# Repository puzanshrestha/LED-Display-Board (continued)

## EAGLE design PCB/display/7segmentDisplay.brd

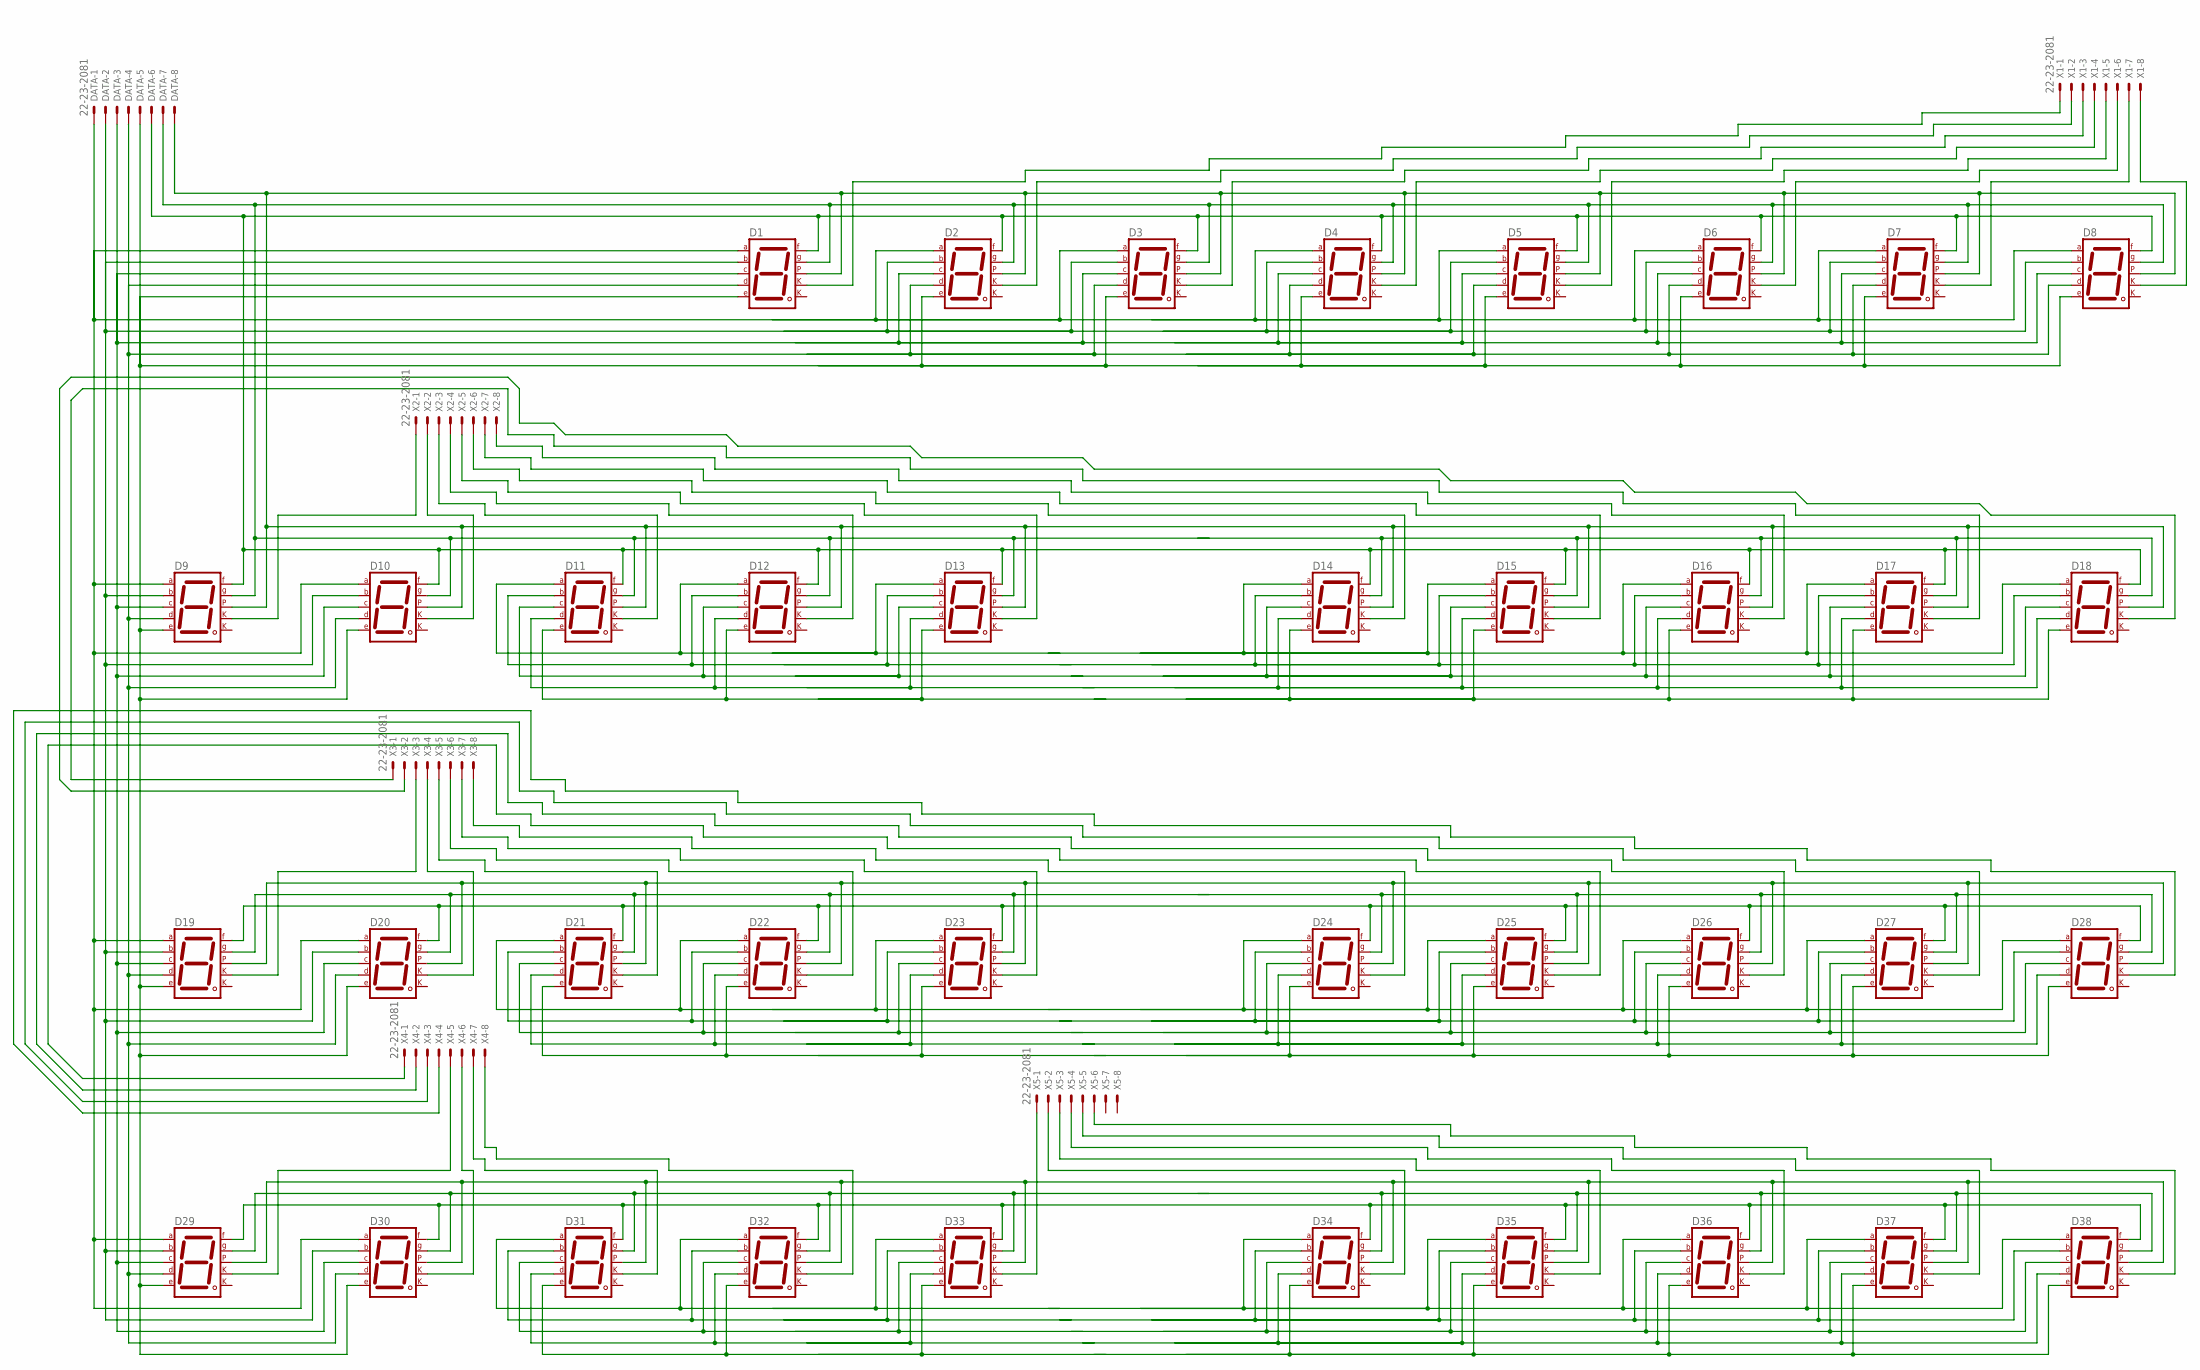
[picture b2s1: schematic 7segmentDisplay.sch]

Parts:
D1, D2, D3, D4, D5, D6, D7, D8, D9, D10, D11, D12, D13, D14, D15, D16, D17, D18, D19, D20, D21, D22, D23, D24, D25, D26, D27, D28, D29, D30, D31, D32, D33, D34, D35, D36, D37, D38: 7SEG-CK; 7SEG-13
DATA: 22-23-2081
X1, X2, X3, X4, X5: 22-23-2081

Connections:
unnamed: D1.7 (A), D2.7 (A), D3.7 (A), D4.7 (A), D5.7 (A), D6.7 (A), D7.7 (A), D8.7 (A), D9.7 (A), D10.7 (A), D19.7 (A), D20.7 (A), D29.7 (A), D30.7 (A), DATA.1
unnamed: D1.6 (B), D2.6 (B), D3.6 (B), D4.6 (B), D5.6 (B), D6.6 (B), D7.6 (B), D8.6 (B), D9.6 (B), D10.6 (B), D19.6 (B), D20.6 (B), D29.6 (B), D30.6 (B), DATA.2
unnamed: D1.4 (C), D2.4 (C), D3.4 (C), D4.4 (C), D5.4 (C), D6.4 (C), D7.4 (C), D8.4 (C), D9.4 (C), D10.4 (C), D19.4 (C), D20.4 (C), D29.4 (C), D30.4 (C), DATA.3
unnamed: D1.2 (D), D2.2 (D), D3.2 (D), D4.2 (D), D5.2 (D), D6.2 (D), D7.2 (D), D8.2 (D), D9.2 (D), D10.2 (D), D19.2 (D), D20.2 (D), D29.2 (D), D30.2 (D), DATA.4
unnamed: D1.1 (E), D2.1 (E), D3.1 (E), D4.1 (E), D5.1 (E), D6.1 (E), D7.1 (E), D8.1 (E), D9.1 (E), D10.1 (E), D19.1 (E), D20.1 (E), D29.1 (E), D30.1 (E), DATA.5
unnamed: D14.10 (G), D15.10 (G), D16.10 (G), D17.10 (G), D18.10 (G)
unnamed: D5.3 (CK1), X1.5
unnamed: D2.3 (CK1), X1.2
unnamed: D3.3 (CK1), X1.3
unnamed: D4.3 (CK1), X1.4
unnamed: D9.3 (CK1), X2.1
unnamed: D6.3 (CK1), X1.6
unnamed: D7.3 (CK1), X1.7
unnamed: D21.7 (A), D22.7 (A), D23.7 (A)
unnamed: D21.6 (B), D22.6 (B), D23.6 (B)
unnamed: D11.7 (A), D12.7 (A), D13.7 (A)
unnamed: D11.6 (B), D12.6 (B), D13.6 (B)
unnamed: D11.4 (C), D12.4 (C), D13.4 (C)
unnamed: D11.2 (D), D12.2 (D), D13.2 (D)
unnamed: D11.1 (E), D12.1 (E), D13.1 (E)
unnamed: D1.9 (F), D2.9 (F), D3.9 (F), D4.9 (F), D5.9 (F), D6.9 (F), D7.9 (F), D8.9 (F), D9.9 (F), D10.9 (F), D11.9 (F), D12.9 (F), D13.9 (F), D14.9 (F), D15.9 (F), D16.9 (F), D17.9 (F), D18.9 (F), DATA.6
unnamed: D1.10 (G), D2.10 (G), D3.10 (G), D4.10 (G), D5.10 (G), D6.10 (G), D7.10 (G), D8.10 (G), D9.10 (G), D10.10 (G), D11.10 (G), D12.10 (G), D13.10 (G), DATA.7
unnamed: D1.5 (DP), D2.5 (DP), D3.5 (DP), D4.5 (DP), D5.5 (DP), D6.5 (DP), D7.5 (DP), D8.5 (DP), D9.5 (DP), D10.5 (DP), D11.5 (DP), D12.5 (DP), D13.5 (DP), D14.5 (DP), D15.5 (DP), D16.5 (DP), D17.5 (DP), D18.5 (DP), DATA.8
unnamed: D8.3 (CK1), X1.8
unnamed: D11.3 (CK1), X2.3
unnamed: D14.7 (A), D15.7 (A), D16.7 (A), D17.7 (A), D18.7 (A)
unnamed: D14.6 (B), D15.6 (B), D16.6 (B), D17.6 (B), D18.6 (B)
unnamed: D14.4 (C), D15.4 (C), D16.4 (C), D17.4 (C), D18.4 (C)
unnamed: D14.2 (D), D15.2 (D), D16.2 (D), D17.2 (D), D18.2 (D)
unnamed: D14.1 (E), D15.1 (E), D16.1 (E), D17.1 (E), D18.1 (E)
unnamed: D21.4 (C), D22.4 (C), D23.4 (C)
unnamed: D21.2 (D), D22.2 (D), D23.2 (D)
unnamed: D21.1 (E), D22.1 (E), D23.1 (E)
unnamed: D19.9 (F), D20.9 (F), D21.9 (F), D22.9 (F), D23.9 (F), D24.9 (F), D25.9 (F), D26.9 (F), D27.9 (F), D28.9 (F)
unnamed: D19.10 (G), D20.10 (G), D21.10 (G), D22.10 (G), D23.10 (G)
unnamed: D19.5 (DP), D20.5 (DP), D21.5 (DP), D22.5 (DP), D23.5 (DP), D24.5 (DP), D25.5 (DP), D26.5 (DP), D27.5 (DP), D28.5 (DP)
unnamed: D12.3 (CK1), X2.4
unnamed: D13.3 (CK1), X2.5
unnamed: D24.7 (A), D25.7 (A), D26.7 (A), D27.7 (A), D28.7 (A)
unnamed: D24.6 (B), D25.6 (B), D26.6 (B), D27.6 (B), D28.6 (B)
unnamed: D24.4 (C), D25.4 (C), D26.4 (C), D27.4 (C), D28.4 (C)
unnamed: D24.2 (D), D25.2 (D), D26.2 (D), D27.2 (D), D28.2 (D)
unnamed: D24.1 (E), D25.1 (E), D26.1 (E), D27.1 (E), D28.1 (E)
unnamed: D24.10 (G), D25.10 (G), D26.10 (G), D27.10 (G), D28.10 (G)
unnamed: D14.3 (CK1), X2.6
unnamed: D15.3 (CK1), X2.7
unnamed: D1.3 (CK1), X1.1
unnamed: D16.3 (CK1), X2.8
unnamed: D18.3 (CK1), X3.2
unnamed: D10.3 (CK1), X2.2
unnamed: D23.3 (CK1), X3.7
unnamed: D31.7 (A), D32.7 (A), D33.7 (A)
unnamed: D31.6 (B), D32.6 (B), D33.6 (B)
unnamed: D31.4 (C), D32.4 (C), D33.4 (C)
unnamed: D31.2 (D), D32.2 (D), D33.2 (D)
unnamed: D31.1 (E), D32.1 (E), D33.1 (E)
unnamed: D29.9 (F), D30.9 (F), D31.9 (F), D32.9 (F), D33.9 (F), D34.9 (F), D35.9 (F), D36.9 (F), D37.9 (F), D38.9 (F)
unnamed: D29.10 (G), D30.10 (G), D31.10 (G), D32.10 (G), D33.10 (G)
unnamed: D29.5 (DP), D30.5 (DP), D31.5 (DP), D32.5 (DP), D33.5 (DP), D34.5 (DP), D35.5 (DP), D36.5 (DP), D37.5 (DP), D38.5 (DP)
unnamed: D19.3 (CK1), X3.3
unnamed: D20.3 (CK1), X3.4
unnamed: D34.7 (A), D35.7 (A), D36.7 (A), D37.7 (A), D38.7 (A)
unnamed: D34.6 (B), D35.6 (B), D36.6 (B), D37.6 (B), D38.6 (B)
unnamed: D34.4 (C), D35.4 (C), D36.4 (C), D37.4 (C), D38.4 (C)
unnamed: D34.2 (D), D35.2 (D), D36.2 (D), D37.2 (D), D38.2 (D)
unnamed: D34.1 (E), D35.1 (E), D36.1 (E), D37.1 (E), D38.1 (E)
unnamed: D34.10 (G), D35.10 (G), D36.10 (G), D37.10 (G), D38.10 (G)
unnamed: D21.3 (CK1), X3.5
unnamed: D22.3 (CK1), X3.6
unnamed: D17.3 (CK1), X3.1
unnamed: D24.3 (CK1), X3.8
unnamed: D25.3 (CK1), X4.1
unnamed: D26.3 (CK1), X4.2
unnamed: D27.3 (CK1), X4.3
unnamed: D28.3 (CK1), X4.4
unnamed: D29.3 (CK1), X4.5
unnamed: D30.3 (CK1), X4.6
unnamed: D31.3 (CK1), X4.7
unnamed: D32.3 (CK1), X4.8
unnamed: D33.3 (CK1), X5.1
unnamed: D34.3 (CK1), X5.2
unnamed: D35.3 (CK1), X5.3
unnamed: D36.3 (CK1), X5.4
unnamed: D37.3 (CK1), X5.5
unnamed: D38.3 (CK1), X5.6

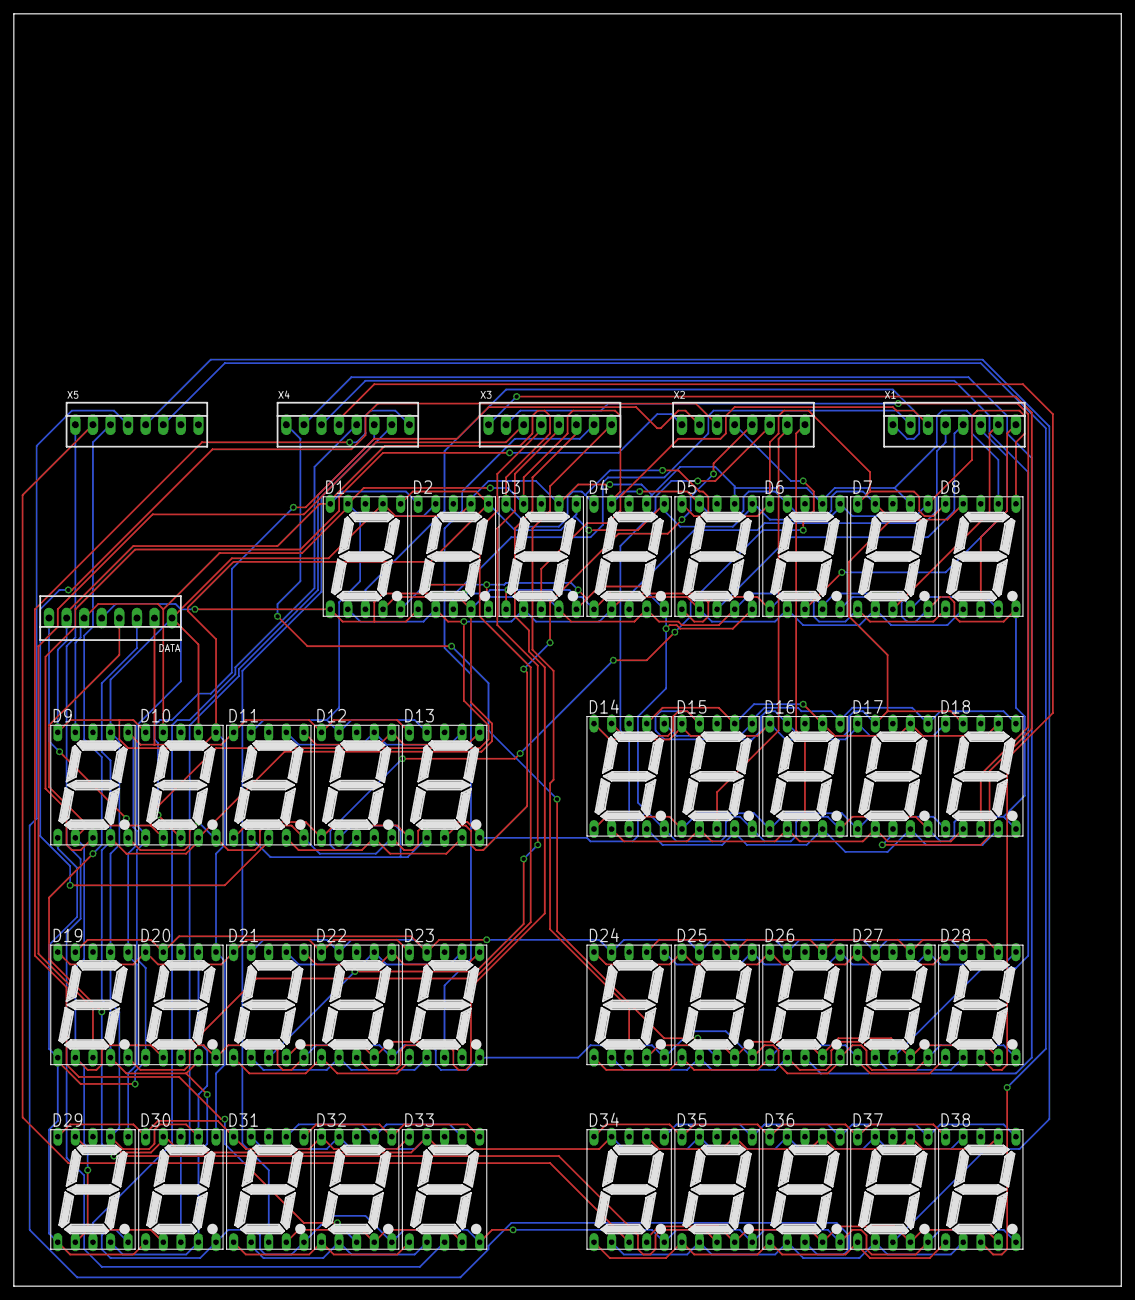
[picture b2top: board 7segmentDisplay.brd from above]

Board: 2 copper layers, 160.0 x 183.8 mm, 44 parts (0 on the bottom side), 85 nets.

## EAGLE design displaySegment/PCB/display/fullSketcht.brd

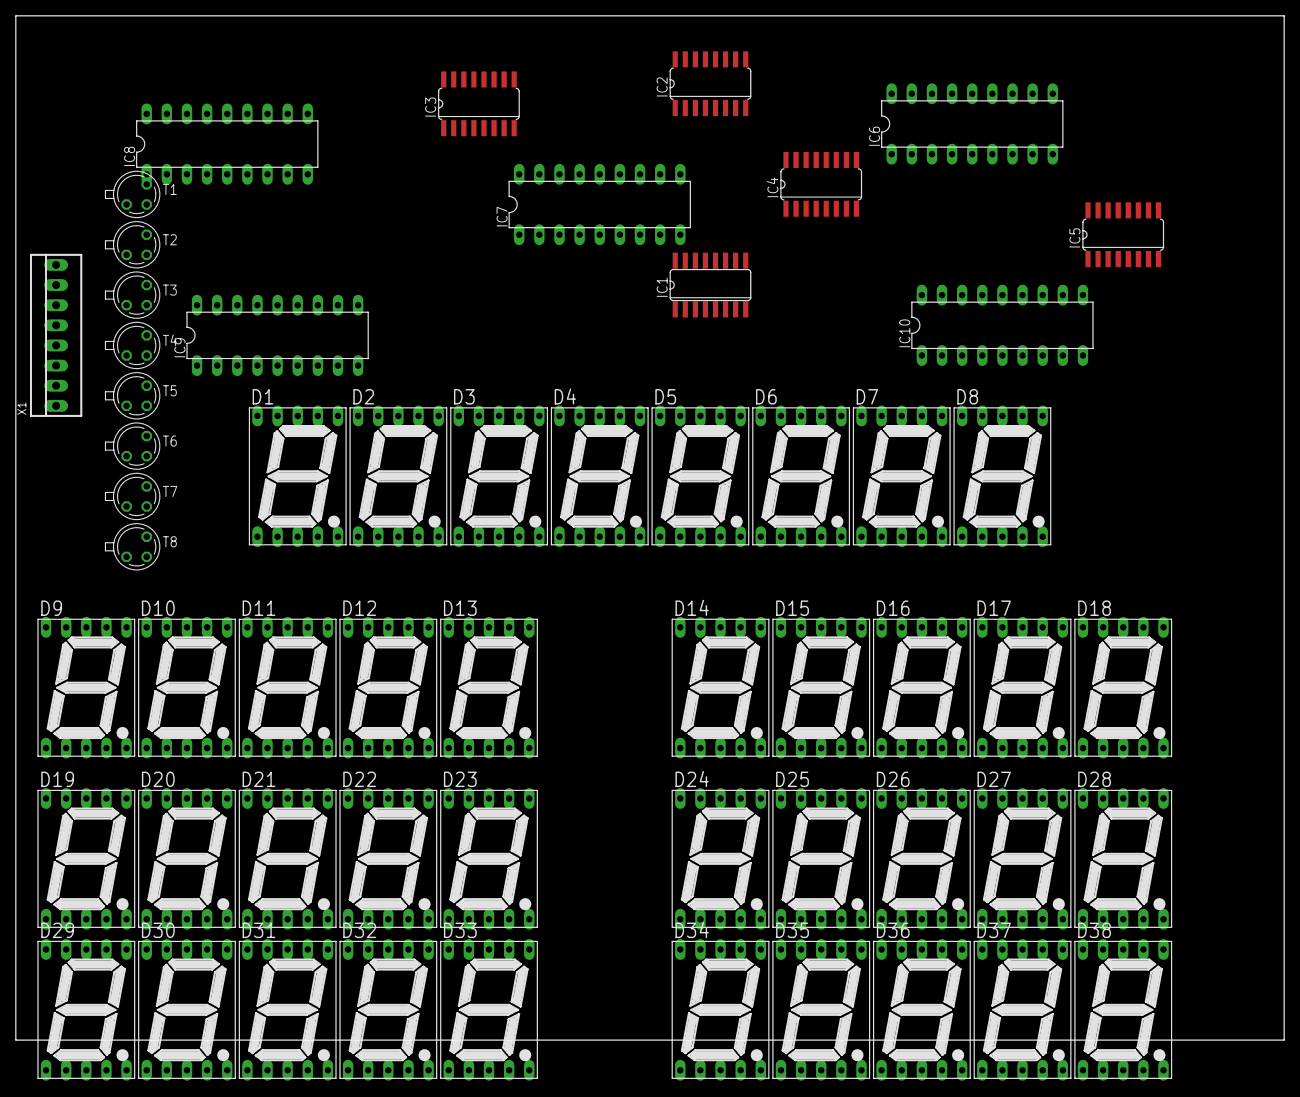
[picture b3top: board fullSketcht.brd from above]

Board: 2 copper layers, 160.0 x 129.2 mm, 57 parts (0 on the bottom side), 103 nets, no tracks yet.

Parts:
D1, D2, D3, D4, D5, D6, D7, D8, D9, D10, D11, D12, D13, D14, D15, D16, D17, D18, D19, D20, D21, D22, D23, D24, D25, D26, D27, D28, D29, D30, D31, D32, D33, D34, D35, D36, D37, D38: 7SEG-13
IC1: 74LS595D; SO16
IC2, IC3, IC4, IC5: 74HC595D; SO16
IC6, IC7, IC8, IC9, IC10: DIL18
T1, T2, T3, T4, T5, T6, T7, T8: 2N2222; TO18
X1: 22-23-2081

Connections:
A: D1.7, D2.7, D3.7, D4.7, D5.7, D6.7, D7.7, D8.7, D9.7, D10.7, D11.7, D12.7, D13.7, D14.7, D15.7, D16.7, D17.7, D18.7, D19.7, D20.7, D21.7, D22.7, D23.7, D24.7, D25.7, D26.7, D27.7, D28.7, D29.7, D30.7, D31.7, D32.7, D33.7, D34.7, D35.7, D36.7, D37.7, D38.7, T1.1
B: D1.6, D2.6, D3.6, D4.6, D5.6, D6.6, D7.6, D8.6, D9.6, D10.6, D11.6, D12.6, D13.6, D14.6, D15.6, D16.6, D17.6, D18.6, D19.6, D20.6, D21.6, D22.6, D23.6, D24.6, D25.6, D26.6, D27.6, D28.6, D29.6, D30.6, D31.6, D32.6, D33.6, D34.6, D35.6, D36.6, D37.6, D38.6, T2.1
B1: T1.2, X1.8
B2: T2.2, X1.7
B3: T3.2, X1.6
B4: T4.2, X1.5
B5: T5.2, X1.4
B6: T6.2, X1.3
B7: T7.2, X1.2
B8: T8.2, X1.1
C: D1.4, D2.4, D3.4, D4.4, D5.4, D6.4, D7.4, D8.4, D9.4, D10.4, D11.4, D12.4, D13.4, D14.4, D15.4, D16.4, D17.4, D18.4, D19.4, D20.4, D21.4, D22.4, D23.4, D24.4, D25.4, D26.4, D27.4, D28.4, D29.4, D30.4, D31.4, D32.4, D33.4, D34.4, D35.4, D36.4, D37.4, D38.4, T3.1
D: D1.2, D2.2, D3.2, D4.2, D5.2, D6.2, D7.2, D8.2, D9.2, D10.2, D11.2, D12.2, D13.2, D14.2, D15.2, D16.2, D17.2, D18.2, D19.2, D20.2, D21.2, D22.2, D23.2, D24.2, D25.2, D26.2, D27.2, D28.2, D29.2, D30.2, D31.2, D32.2, D33.2, D34.2, D35.2, D36.2, D37.2, D38.2, T4.1
E: D1.1, D2.1, D3.1, D4.1, D5.1, D6.1, D7.1, D8.1, D9.1, D10.1, D11.1, D12.1, D13.1, D14.1, D15.1, D16.1, D17.1, D18.1, D19.1, D20.1, D21.1, D22.1, D23.1, D24.1, D25.1, D26.1, D27.1, D28.1, D29.1, D30.1, D31.1, D32.1, D33.1, D34.1, D35.1, D36.1, D37.1, D38.1, T5.1
F: D1.9, D2.9, D3.9, D4.9, D5.9, D6.9, D7.9, D8.9, D9.9, D10.9, D11.9, D12.9, D13.9, D14.9, D15.9, D16.9, D17.9, D18.9, D19.9, D20.9, D21.9, D22.9, D23.9, D24.9, D25.9, D26.9, D27.9, D28.9, D29.9, D30.9, D31.9, D32.9, D33.9, D34.9, D35.9, D36.9, D37.9, D38.9, T6.1
G: D1.10, D2.10, D3.10, D4.10, D5.10, D6.10, D7.10, D8.10, D9.10, D10.10, D11.10, D12.10, D13.10, D14.10, D15.10, D16.10, D17.10, D18.10, D19.10, D20.10, D21.10, D22.10, D23.10, D24.10, D25.10, D26.10, D27.10, D28.10, D29.10, D30.10, D31.10, D32.10, D33.10, D34.10, D35.10, D36.10, D37.10, D38.10, T7.1
GND: IC1.8, IC1.13, IC2.8, IC2.13, IC3.8, IC3.13, IC4.8, IC4.13, IC5.8, IC5.13, IC6.9, IC7.9, IC8.9, IC9.9, IC10.9
H: D1.5, D2.5, D3.5, D4.5, D5.5, D6.5, D7.5, D8.5, D9.5, D10.5, D11.5, D12.5, D13.5, D14.5, D15.5, D16.5, D17.5, D18.5, D19.5, D20.5, D21.5, D22.5, D23.5, D24.5, D25.5, D26.5, D27.5, D28.5, D29.5, D30.5, D31.5, D32.5, D33.5, D34.5, D35.5, D36.5, D37.5, D38.5, T8.1
MR: IC1.10, IC2.10, IC3.10, IC4.10, IC5.10
unnamed: IC1.15, IC6.1
unnamed: IC1.1, IC6.2
unnamed: IC1.2, IC6.3
unnamed: IC1.3, IC6.4
unnamed: IC1.4, IC6.5
unnamed: IC1.5, IC6.6
unnamed: IC1.6, IC6.7
unnamed: IC1.7, IC6.8
unnamed: IC1.9, IC2.14
unnamed: IC2.15, IC7.1
unnamed: IC2.1, IC7.2
unnamed: IC2.2, IC7.3
unnamed: IC2.3, IC7.4
unnamed: IC2.4, IC7.5
unnamed: IC2.5, IC7.6
unnamed: IC2.6, IC7.7
unnamed: IC2.7, IC7.8
unnamed: IC2.9, IC3.14
unnamed: IC3.15, IC8.1
unnamed: IC3.1, IC8.2
unnamed: IC3.2, IC8.3
unnamed: IC3.3, IC8.4
unnamed: IC3.4, IC8.5
unnamed: IC3.5, IC8.6
unnamed: IC3.6, IC8.7
unnamed: IC3.7, IC8.8
unnamed: IC3.9, IC4.14
unnamed: IC4.15, IC9.1
unnamed: IC4.1, IC9.2
unnamed: IC4.2, IC9.3
unnamed: IC4.3, IC9.4
unnamed: IC4.4, IC9.5
unnamed: IC4.5, IC9.6
unnamed: IC4.6, IC9.7
unnamed: IC4.7, IC9.8
unnamed: IC4.9, IC5.14
unnamed: IC5.15, IC10.1
unnamed: IC5.1, IC10.2
unnamed: IC5.2, IC10.3
unnamed: IC5.3, IC10.4
unnamed: IC5.4, IC10.5
unnamed: IC5.5, IC10.6
unnamed: IC5.6, IC10.7
unnamed: IC5.7, IC10.8
SEG1: D1.3, IC6.18
SEG2: D2.3, IC6.17
SEG3: D3.3, IC6.16
SEG4: D4.3, IC6.15
SEG5: D5.3, IC6.14
SEG6: D6.3, IC6.13
SEG7: D7.3, IC6.12
SEG8: D8.3, IC6.11
SEG9: D9.3, IC7.18
SEG10: D10.3, IC7.17
SEG11: D11.3, IC7.16
SEG12: D12.3, IC7.15
SEG13: D13.3, IC7.14
SEG14: D14.3, IC7.13
SEG15: D15.3, IC7.12
SEG16: D16.3, IC7.11
SEG17: D17.3, IC8.18
SEG18: D18.3, IC8.17
SEG19: D19.3, IC8.16
SEG20: D20.3, IC8.15
SEG21: D21.3, IC8.14
SEG22: D22.3, IC8.13
SEG23: D23.3, IC8.12
SEG24: D24.3, IC8.11
SEG25: D25.3, IC9.18
SEG26: D26.3, IC9.17
SEG27: D27.3, IC9.16
SEG28: D28.3, IC9.15
SEG29: D29.3, IC9.14
SEG30: D30.3, IC9.13
SEG31: D31.3, IC9.12
SEG32: D32.3, IC9.11
SEG33: D33.3, IC10.18
SEG34: D34.3, IC10.17
SEG35: D35.3, IC10.16
SEG36: D36.3, IC10.15
SEG37: D37.3, IC10.14
SEG38: D38.3, IC10.13
SH_CP: IC1.11, IC2.11, IC3.11, IC4.11, IC5.11
ST_CP: IC1.12, IC2.12, IC3.12, IC4.12, IC5.12
VCC: IC1.16, IC2.16, IC3.16, IC4.16, IC5.16, IC6.10, IC7.10, IC8.10, IC9.10, IC10.10, T1.3, T2.3, T3.3, T4.3, T5.3, T6.3, T7.3, T8.3

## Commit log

2018-11-13 initialization
2019-09-24 init folder
2019-09-28 init files
2019-09-28 discard
2019-09-28 organize file structure
2019-09-28 set file structure
